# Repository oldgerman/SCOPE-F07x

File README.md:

# [SCOPE-F07x](https://github.com/oldgerman/SCOPE-F07x)

### 关于

[SCOPE-F07x](https://github.com/oldgerman/SCOPE-F07x) 从 [硬禾SCOPE-F072](https://github.com/EETree-git/SCOPE-F072) 开源和公开资料修改&优化

零零散散修改的地方比较多，详见修改说明部分

### PCB

工艺：

- 层数：2
- 板厚: 1.0mm 
- 过孔: 0.3/0.5mm
- 线宽线隙: 6mil/6mil
- 尺寸: 38x38mm

封装：绝大多数是0402，物料约40多种

|  |  |  |  |
| -------------------- | -------------------- | ------------------------ | ------------------------ |

### 外壳

硬禾的原始设计配套的外壳有亿点点low，出于情怀我想到经典设计 iPod nano (*6th* generation)，然而想做到这么简约并非易事

经过PCB和建模的各方面努力，外壳OK

- 屏幕完美居中
- 结构针对FDM成型进行了很多优化，打印全程无需支撑和拉桥
- 外壳平均厚度为2mm，免螺丝设计，纯卡扣固定，实测上下壳体卡得极其牢固

|  |  |
| ------------------------- | ------------------------- |

一张 iPod nano 6th 海报同款角度视图 (๑•̀ㅂ•́)و✧

### 散热

OPA4197其中的两个运放作为双路直流电压源，电流范围±30mA，手册 I(sink)和I(source)给的是±65mA，实测输出3.3V电压，负载电流30mA时，没有什么压降，但发热比较大，当增加到40mA开始过热/失调，电压不再稳定，因此推荐加装散热片

散热片物料：15x15x0.5mm紫铜片、3M 8810导热双面胶、金手指胶带

| .jpeg)        | .jpeg)          |
| ------------------------------------------------------------ | ------------------------------------------------ |
| OPA4197的TSSOP-14封装比较薄，保险起见可以用金手指胶带封住一部分，防止短路，虽然实际距离还挺宽裕 | 将导热胶裁剪至合适大小，之后对准中心贴上铜片即可 |

### 修改说明

#### 硬件

| 部分     | 原版                                                         | 修改                                                         |
| -------- | ------------------------------------------------------------ | ------------------------------------------------------------ |
| Layout   | STM32的模拟和数字共用电源和地，运放有个单独的3.0V电源（不明白为啥不拿这个给STM32的VDDA也供电，猜测因为STM32模拟供电电压要高于数字部分，但是3.0V又比3.3V低了0.3V不合格） | 模数电源和地分离。模拟部分电源从3.0V改为3.3V，也为STM32的VDDA供电，因为这0.3V的变化，运放电路电阻取值经过重新计算，与EEtree的技术指标保持一致 |
| USB      | Miro USB，仅USB功能                                          | Type-c 正反插功能不同，正插USB DFU，反插可以用stlink调试（D+: SWCLK，D-: SWDIO） |
| 运放     | TP2302                                                       | TP2302运放太冷门买不到，改为SGM8632                          |
|          | TL974                                                        | TL974 I(source)太弱了只有1.5mA，改为OPA4197                  |
| STM32    | STM32F072CBT6                                                | 换为QFN-48封装，引脚变更较多，兼容STM32F071、STM32F072，071虽然手册没写有USB但是出厂固件的 USB DFU 都有，071当072烧固件USB功能都是完整的，071就是072 |
| 电荷泵   | LM2776                                                       | LM2776过于昂贵，换为便宜很多的SGM3204                        |
| 加速度计 | MMA8653                                                      | MMA8653又贵又冷门，换为LIS3DH，拆机的都降价到1元包邮啦       |
| EEPROM   | 24C01                                                        | 换为SOT-23封装，容量大小任意                                 |
| 按键     | 2个按键 + 拨轮开关                                           | 拨轮开关换为3个按键，一共5个按键                             |

备注：其他修改细节见原理图

#### 软件

原版程序：

有好几个大的数组(成员数量几百个)，使用静态内存分配，运行时不能释放，导致固件编译后内存使用率95%以上，开Os优化编译后，Flash可用空间还有50KB以上，由于RAM剩余空间紧张，加速度计、EEPROM、屏幕背光、USB通讯、ADC反馈等相关实现被裁剪

优化目标：

使用动态内存分配，尽可能实现上述被裁剪的功能

代码进度：

目前仅针对修改版PCB做了修改适配，提供工程源码文件，优化还没开始搞，代码等改好了有空再说~

### 功能测试

| 反向放大电路：提供正负电源+信号源、并测量放大后的信号  | 可调电压源双路输出20mA-30mA                                  | 可调电压源输出负4V                                           |
| ------------------------------------------------------ | ------------------------------------------------------------ | ------------------------------------------------------------ |
|  |  |  |

| 设定频率 | 设定电压 | 三角波                                                       | 方波                                                         | 正弦波                                                       |
| -------- | -------- | ------------------------------------------------------------ | ------------------------------------------------------------ | ------------------------------------------------------------ |
| 100KHz   | ±100mV   | .jpeg) | .jpeg) | .jpeg) |
| 10KHz    | ±4.0V    | .jpeg)              | .jpeg)              | .jpeg)              |
| 100KHz   | ±4.0V    | .jpeg)            | .jpeg)            | .jpeg)            |

### 其他&补充

**一些目录说明**

- [AD工程](https://github.com/oldgerman/SCOPE-F07x/tree/master/HardWare/AD_Project)：提供可编辑的源文件，软件版本2019，PDF的原理图也位于此目录

- [SW工程](https://github.com/oldgerman/SCOPE-F07x/tree/master/HardWare/SW_Project)：提供可编辑的源文件，软件版本2017

- [外壳3D打印模型](https://github.com/oldgerman/SCOPE-F07x/tree/master/HardWare/3D_Print)：STL格式提供，打印一套外壳的话，其中`SW_x3_Both_Sides_1.STL`需要打两个
- [BOM](https://github.com/oldgerman/SCOPE-F07x/tree/master/HardWare/BOM/bom)：浏览器可直接打开的交互式BOM
- [Gerber](https://github.com/oldgerman/SCOPE-F07x/tree/master/HardWare/Gerber)：整个压缩包就是
- [朋友们制作的成品展示](https://github.com/oldgerman/SCOPE-F07x/tree/master/朋友们自驾的成品)

**按键操作**

- KEY_1: 单击切换功能页面
- KEY_2: 单击切换子菜单光标
- KEY_R: 减少值或向左移动
- KEY_O: 确认或取消
- KEY_L: 增大值或向右移动

**USB DFU**

需要在未上电时按住KEY_O不放，插电进入，推荐使用STM32CubeProgrammer的USB模式烧录

### Acknowledgments

感谢硬禾团队

### License

This work is licensed under a
[Creative Commons Attribution-NonCommercial-ShareAlike 4.0 International License][cc-by-nc-sa].

[![CC BY-NC-SA 4.0][cc-by-nc-sa-image]][cc-by-nc-sa]

[cc-by-nc-sa]: http://creativecommons.org/licenses/by-nc-sa/4.0/
[cc-by-nc-sa-image]: https://i.creativecommons.org/l/by-nc-sa/4.0/88x31.png

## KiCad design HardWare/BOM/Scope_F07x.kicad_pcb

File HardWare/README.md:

## AD工程

软件版本2019

## SW工程

软件版本2017

## 3D打印模型

3D_Print文件夹STL格式提供，打印一套外壳的话，其中SW_x3_Both_Sides_1需要打两个

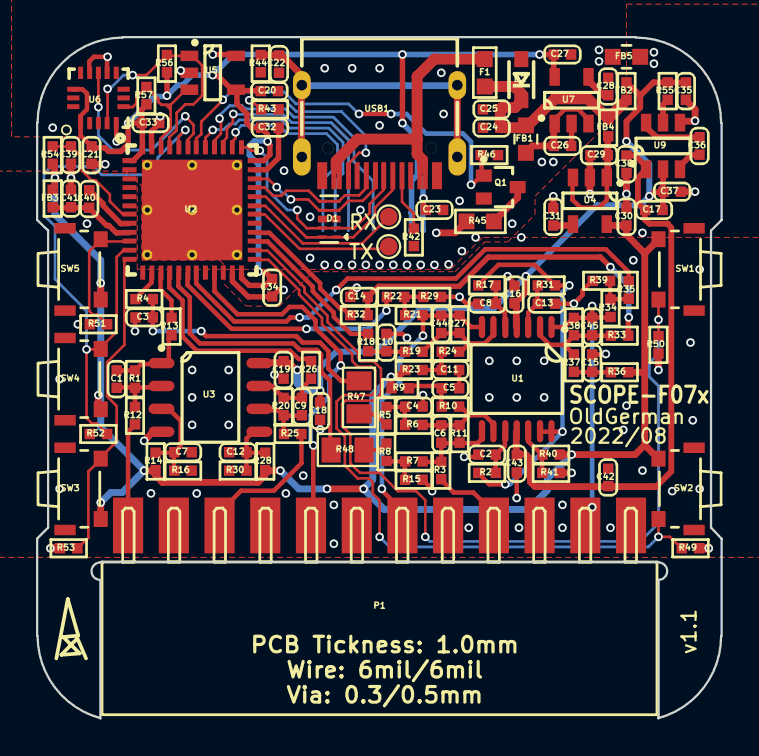
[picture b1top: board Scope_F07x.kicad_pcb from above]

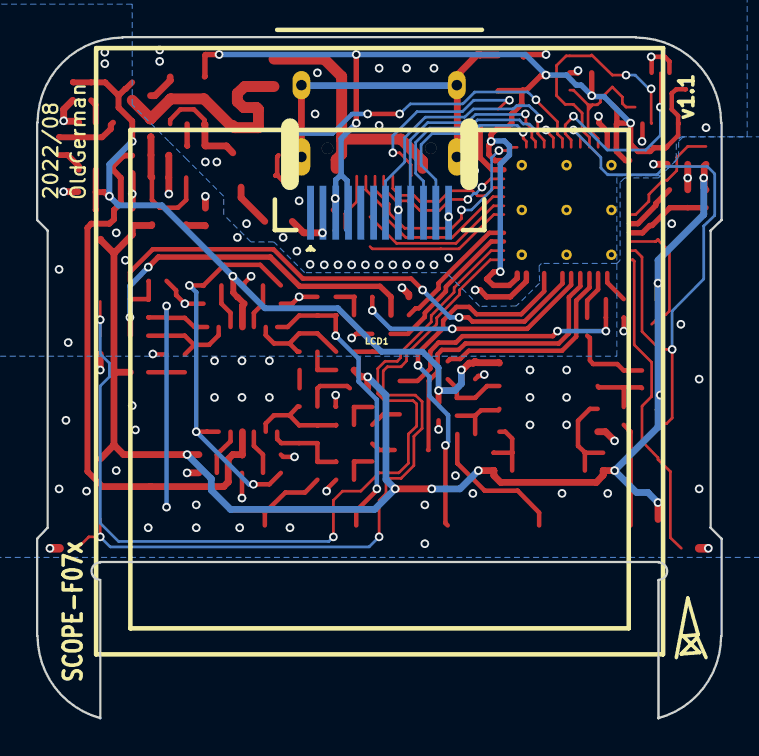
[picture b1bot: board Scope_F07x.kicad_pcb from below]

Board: 2 copper layers, 38.0 x 37.8 mm, 129 parts (2 on the bottom side), 80 nets.

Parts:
C1, C9: 0.5pF; C0402_1
C2, C5, C8, C10, C11, C13, C14, C15, C25, C40: 1uF; C0402_1
C3, C4: 150pF; C0402_1
C6: 39pF; C0402_1
C7, C12, C36, C37, C38: 4.7uF; C0402_1
C16, C17, C19, C20, C23, C32, C33, C34, C39, C43: 100nF; C0402_1
C18, C21, C24, C26, C27, C29, C30, C35, C41, C42: 10uF; C0402_1
C22: 4.7nF; C0402_1
C28, C44, C45: DNP; C0402_1
C31: 22nF; C0402_1
D1: PESD1LVDS; DFN2510-10_SOT1165-1_1
D2: SD05; SOD-323_1
F1: 6V/500mA; FUSE0603_0.5MM_1
FB1: 330R @100MHz; FER0603_2
FB2, FB3, FB4: 220R @100MHz; FER0402_1
FB5: 330R @100MHz; FER0603_1
LCD1: LCD_240x240; LCD-240X240-1.54INCH_FLUSH_F74
ODG1, ODG2: ODG_LOGO; ODG_LOGO_1
P1: CONN_X12; 2.54MM_FEMALE_1x12_180H_1
Q1: 2N7002KW; DIODES_SOT-323-3_1
R1, R20: 330K; R0402_1
R2, R7, R10, R17, R21, R31, R34: 1K; R0402_1
R3: 49.9R; R0402_1
R4: 536R; R0402_1
R5: 750R; R0402_1
R6: 270R; R0402_1
R8, R22, R24, R35, R37, R46, R54, R55: 10K; R0402_1
R9, R16, R18, R30, R32: 3.3K; R0402_1
R11: 4.3K; R0402_1
R12, R25, R44: 1M; R0402_1
R13, R26: 100R; R0402_1
R14, R28: 5.49K; R0402_1
R15, R23, R29, R36, R39: 2K; R0402_1
R19, R33: 1.65K; R0402_1
R27, R38, R40, R41: 12K; R0402_1
R42, R43: 5.1K; R0402_1
R45: 10R; R0603_1
R47, R48: 0R; R0805_1
R49, R50, R51, R52, R53, R56, R57: 4.7K; R0402_1
SW1, SW2, SW3, SW4, SW5: Button-2P+PAD; TACTILE_SWITCH_SMD_4.6x1.82x32
U1: OPA4197; ON_SEMI_TSSOP-14_948G_1
U2: STM32F072CBU6 / STM32F071CBU6; UFQFPN-48_7X7X0P55MM_VIA_1
U3: SGM8632; ANALOG_DEV_SOIC-8_R8_1
U4: RT9193-33GB; MICROCHIP_SOT-23-5_OT_1
U5: 24Cxx_SOT23-5; MICROCHIP_SOT-23-5_OT_1
U6: LIS3DH; LGA-16-3X3_1
U7: ME6211C33M5G; ANALOG_TSOT-23-5_UJ-5_1
U9: SGM3204YN6G/TR; MICROCHIP_SOT-23-6_M6_1
USB1: Type-C; Type-C-TOP_1

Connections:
AGND: C2.2, C3.1, C4.1, C5.1, C7.1, C8.2, C10.1, C11.1, C12.1, C13.2, C14.1, C15.1, C16.1, C18.1, C19.1, C29.2, C30.2, C31.2, C35.1, C37.2, C38.2, C39.2, C40.2, C41.2, C42.1, C43.1, FB5.2, P1.1, P1.3, P1.5, P1.7, P1.9, P1.11, R15.1, R16.1, R29.1, R30.1, R39.1, R41.1, R49.2, R50.2, R51.2, R52.2, R53.2, U2.8, U3.4, U4.2, U9.4
CC1: R42.1, USB1.A5
CC2: R43.2, USB1.B5
D+_A6: D1.2, D1.9, U2.37, USB1.A6
D+_B6: D1.5, D1.6, U2.33, USB1.B6
D-_A7: D1.4, D1.7, U2.34, USB1.A7
D-_B7: D1.1, D1.10, U2.32, USB1.B7
GND: C20.2, C21.2, C22.2, C23.1, C24.2, C25.2, C26.2, C27.2, C28.2, C32.2, C33.2, C34.2, D1.3, D1.8, D2.1, FB5.1, LCD1.1, LCD1.5, LCD1.6, LCD1.8, LCD1.12, Q1.2, R42.2, R43.1, R44.2, R46.1, U2.23, U2.35, U2.47, U2.49, U2.49_1, U2.49_2, U2.49_3, U2.49_4, U2.49_5, U2.49_6, U2.49_7, U2.49_8, U2.49_9, U5.2, U5.5, U6.5, U6.10, U6.12, U7.2, USB1.A1, USB1.A12, USB1.B1, USB1.B12
KEY_L: R51.1, SW5.2, U2.10
KEY_O: R52.1, SW4.2, U2.11, U2.44
KEY_R: R53.1, SW3.2, U2.12
LCD_BL: Q1.1, R46.2, U2.42
LCD_DC: LCD1.7, U2.40
LCD_LEDK: LCD1.2, R45.2
LCD_MOSI: LCD1.10, U2.41
LCD_RSTn: LCD1.11, U2.38
LCD_SCK: LCD1.9, U2.39
MEM_SCL: R56.2, U2.45, U5.1, U6.4
MEM_SDA: R57.2, U2.46, U5.3, U6.6
NetC1_1: C1.1, R1.2, R13.1, U3.1
NetC1_2: C1.2, R1.1, R12.2, U3.2
NetC2_1: C2.1, R2.2, U1.10
NetC3_2: C3.2, R4.2, R47.1
NetC4_2: C4.2, R5.2, R6.1
NetC5_2: C5.2, R9.2, R10.1
NetC6_1: C6.1, R3.1, R7.2, R11.2, U1.8
NetC6_2: C6.2, R6.2, R10.2, R11.1, U1.9
NetC7_2: C7.2, R14.2, R16.2, U3.3
NetC8_1: C8.1, R17.2, U1.5
NetC9_1: C9.1, R20.2, R26.1, U3.7
NetC9_2: C9.2, R20.1, R25.2, U3.6
NetC10_2: C10.2, R18.2, R19.1
NetC11_2: C11.2, R23.2, R24.1
NetC12_2: C12.2, R28.2, R30.2, U3.5
NetC13_1: C13.1, R31.2, U1.3
NetC14_2: C14.2, R32.2, R33.1
NetC15_2: C15.2, R36.2, R37.1
NetC22_1: C22.1, R44.1, USB1.1, USB1.2, USB1.3, USB1.4
NetC26_1: C26.1, FB1.2, U7.1, U7.3
NetC28_1: C28.1, U7.4
NetC29_1: C29.1, FB4.2, U4.1, U4.3
NetC31_1: C31.1, U4.4
NetC36_1: C36.1, U9.3
NetC36_2: C36.2, U9.6
NetC39_1: C39.1, R54.2, U2.7
NetC40_1: C40.1, C41.1, FB3.2, U2.9
NetC44_1: C44.1, P1.6, R21.2, R27.2, U1.7
NetC44_2: C44.2, R19.2, R24.2, R27.1, U1.6
NetC45_1: C45.1, P1.2, R34.2, R38.2, U1.1
NetC45_2: C45.2, R33.2, R37.2, R38.1, U1.2
NetP1_4: P1.4, R3.2
NetP1_8: P1.8, U2.21
NetP1_10: P1.10, R25.1
NetP1_12: P1.12, R12.1
NetQ1_3: Q1.3, R45.1
NetR4_1: R4.1, U2.14
NetR5_1: R5.1, R47.2
NetR7_1: R7.1, R8.2, R15.2
NetR8_1: R8.1, R48.1
NetR13_2: R13.2, U2.15
NetR18_1: R18.1, U2.27
NetR21_1: R21.1, R22.2, R29.2
NetR22_1: R22.1, U2.18
NetR26_2: R26.2, U2.16
NetR32_1: R32.1, U2.28
NetR34_1: R34.1, R35.2, R39.2
NetR35_1: R35.1, U2.19
NetR40_2: R40.2, R41.2, U1.12
NetR48_2: R48.2, U2.17
NetR49_1: R49.1, SW2.2, U2.25
NetR50_1: R50.1, SW1.2, U2.26
NetR55_1: R55.1, U9.5
NetU2_43: U2.43, U6.11
VCC_3V3: C20.1, C21.1, C23.2, C27.1, C32.1, C33.1, C34.1, LCD1.3, LCD1.4, R56.1, R57.1, U2.1, U2.24, U2.36, U2.48, U5.4, U6.1, U6.14, U7.5
VDA_1V65: R2.1, R17.1, R31.1, U1.13, U1.14
VDA_3V3: C30.1, FB3.1, R9.1, R14.1, R23.1, R28.1, R36.1, R40.1, R54.1, SW1.1, SW2.1, SW3.1, SW4.1, SW5.1, U4.5
VDA_5V0: C16.2, C17.2, C18.2, C19.2, C35.2, C37.1, FB2.1, R55.2, U1.4, U3.8, U9.2
VDA_-5V0: C17.1, C38.1, C42.2, C43.2, U1.11, U9.1
VUSB: F1.1, USB1.A4, USB1.A9, USB1.B4, USB1.B9
VUSB_5V: C24.1, C25.1, D2.2, F1.2, FB1.1, FB2.2, FB4.1

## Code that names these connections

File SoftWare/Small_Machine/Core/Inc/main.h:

/* USER CODE BEGIN Header */
/**
  ******************************************************************************
  * @file           : main.h
  * @brief          : Header for main.c file.
  *                   This file contains the common defines of the application.
  ******************************************************************************
  * @attention
  *
  * <h2><center>&copy; Copyright (c) 2021 STMicroelectronics.
  * All rights reserved.</center></h2>
  *
  * This software component is licensed by ST under BSD 3-Clause license,
  * the "License"; You may not use this file except in compliance with the
  * License. You may obtain a copy of the License at:
  *                        opensource.org/licenses/BSD-3-Clause
  *
  ******************************************************************************
  */
/* USER CODE END Header */

/* Define to prevent recursive inclusion -------------------------------------*/
#ifndef __MAIN_H
#define __MAIN_H

#ifdef __cplusplus
extern "C" {
#endif

/* Includes ------------------------------------------------------------------*/
#include "stm32f0xx_hal.h"

/* Private includes ----------------------------------------------------------*/
/* USER CODE BEGIN Includes */

/* USER CODE END Includes */

/* Exported types ------------------------------------------------------------*/
/* USER CODE BEGIN ET */

/* USER CODE END ET */

/* Exported constants --------------------------------------------------------*/
/* USER CODE BEGIN EC */

/* USER CODE END EC */

/* Exported macro ------------------------------------------------------------*/
/* USER CODE BEGIN EM */

/* USER CODE END EM */

/* Exported functions prototypes ---------------------------------------------*/
void Error_Handler(void);

/* USER CODE BEGIN EFP */

/* USER CODE END EFP */

/* Private defines -----------------------------------------------------------*/
#define Key_1_Pin GPIO_PIN_13
#define Key_1_GPIO_Port GPIOB

#define Key_2_Pin GPIO_PIN_12
#define Key_2_GPIO_Port GPIOB

#define Key_R_Pin GPIO_PIN_2
#define Key_R_GPIO_Port GPIOA

#define Key_O_Pin GPIO_PIN_1
#define Key_O_GPIO_Port GPIOA

#define Key_L_Pin GPIO_PIN_0
#define Key_L_GPIO_Port GPIOA

#define LCD_DC_Pin GPIO_PIN_4
#define LCD_DC_GPIO_Port GPIOB

#define LCD_SCL_Pin GPIO_PIN_3
#define LCD_SCL_GPIO_Port GPIOB

#define LCD_RST_Pin GPIO_PIN_15
#define LCD_RST_GPIO_Port GPIOA

#define LCD_SDA_Pin GPIO_PIN_5
#define LCD_SDA_GPIO_Port GPIOB

#define LCD_BL_Pin GPIO_PIN_6
#define LCD_BL_GPIO_Port GPIOB
/* USER CODE BEGIN Private defines */

/* USER CODE END Private defines */

#ifdef __cplusplus
}
#endif

#endif /* __MAIN_H */

/************************ (C) COPYRIGHT STMicroelectronics *****END OF FILE****/

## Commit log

2022-08-02 添加EETree仓库链接
2022-08-02 补充README说明
2022-08-10 PCB更新v1.1版本
2022-08-10 添加鸣谢
2022-08-10 添加README.pdf
2022-08-10 添加Gerber,移动BOM目录
2022-08-11 R4从750R修改为536R，原因是DAC输出缓冲器不是轨到轨，通过减小R4增加增益解决
2022-08-11 移除部分手册
2022-08-12 RT9393更正为RT9193，添加3d打印模型
2022-08-12 补充README，添加License
2022-08-12 补充README
2022-08-12 添加SW_Project、LTspice
2022-08-12 移除NANO文件夹
2022-08-12 更新bin
2022-08-14 更新750R换536R的固件，发生信号的摆幅可以到-4V~4V
2022-08-14 功能测试-添加波形发生
2022-08-16 功能测试-添加图片
2022-08-18 修正原理图注释错误
2023-04-26 2023-04-26_02:46 修复CH2频率计不显示和printf动态内存死机问题
2023-04-26 2023-04-26_02:50
2023-07-02 2023-07-02_18:16
2024-03-20 2024-0320_22:23
